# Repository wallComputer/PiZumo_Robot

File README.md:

# PiZumo_Robot

Git Folder to share hardware and software files for PiZumo Robot.

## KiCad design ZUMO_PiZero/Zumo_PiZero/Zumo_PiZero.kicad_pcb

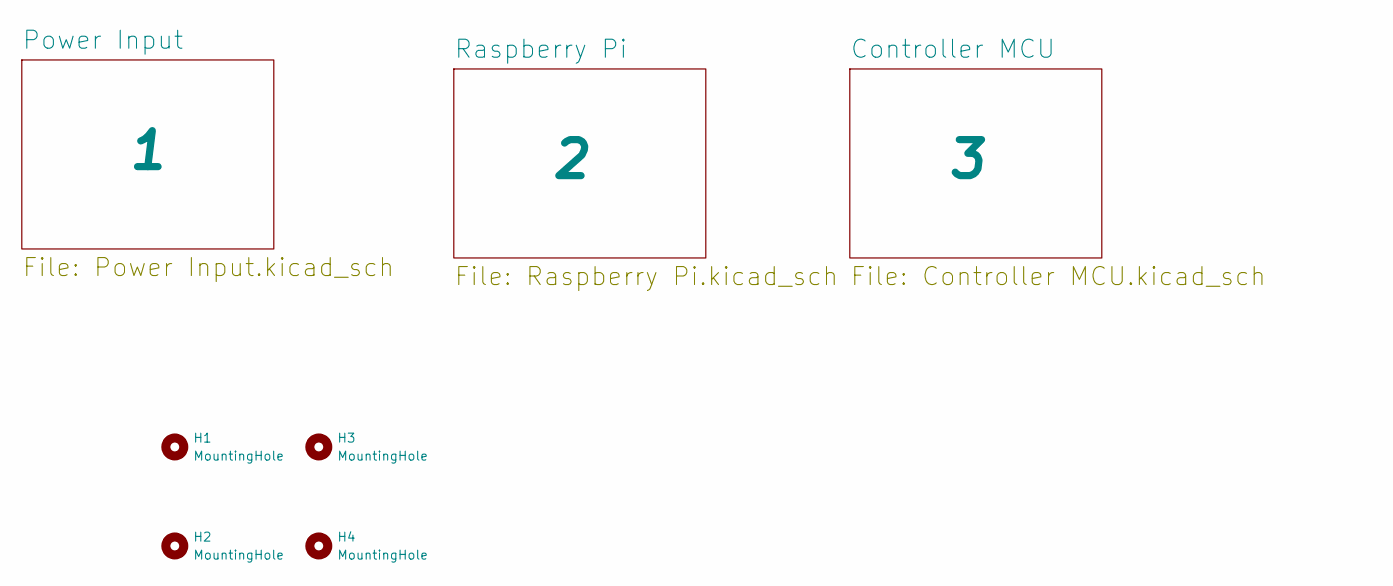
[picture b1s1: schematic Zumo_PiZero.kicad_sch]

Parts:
H1, H2, H3, H4: MountingHole; Zumo_Padded_Holes

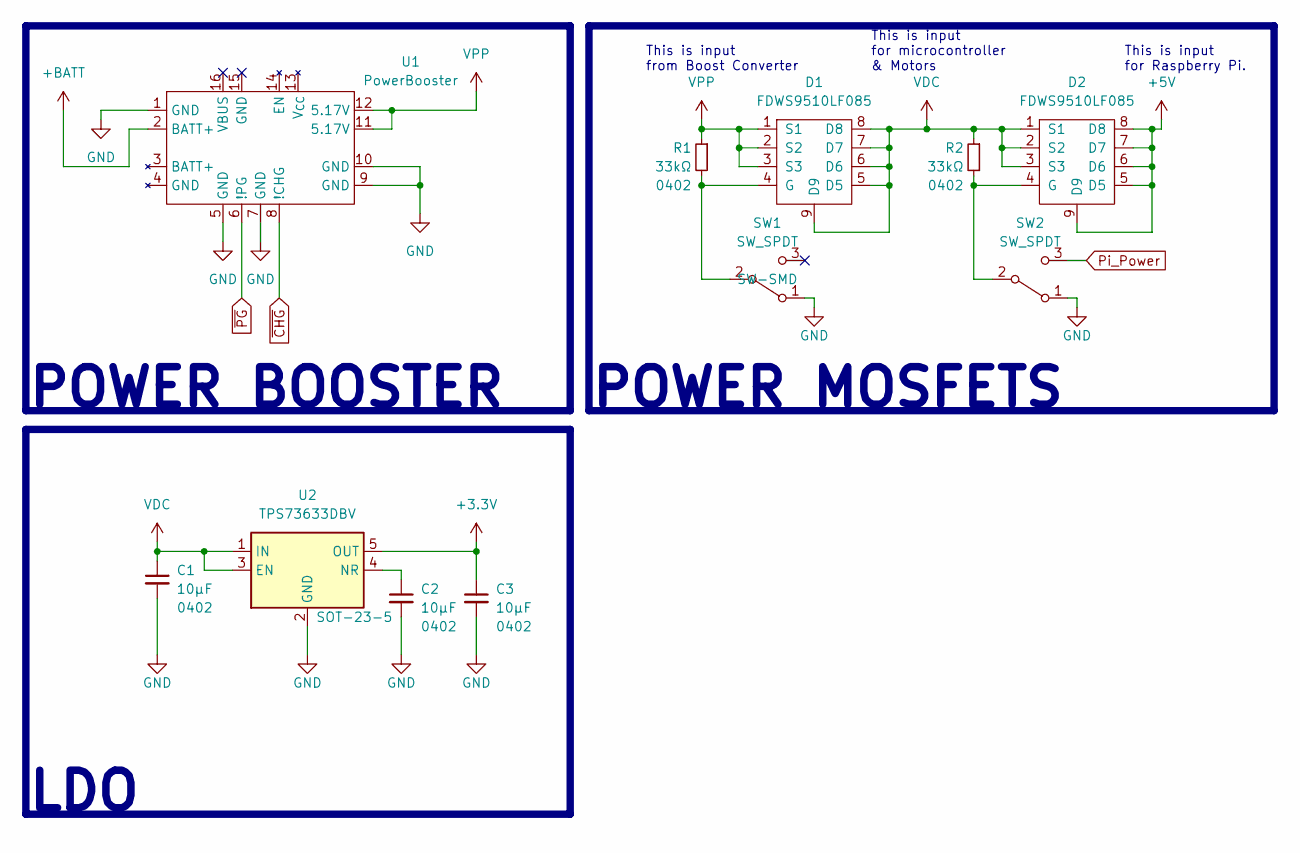
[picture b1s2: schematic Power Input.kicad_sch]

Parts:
C1, C2, C3: 10µF; C_0402_1005Metric; JLC 0402
D1, D2: FDWS9510LF085
R1, R2: 33kΩ; R_0402_1005Metric; JLC 0402
SW1, SW2: SW_SPDT; SW_SPDT_PCM12; JLC SW-SMD
U1: PowerBooster
U2: TPS73633DBV; SOT-23-5; JLC SOT-23-5

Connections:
+3V3: C3.1, U2.5 (OUT); also elsewhere on the board
+5V: D2.5 (D5), D2.6 (D6), D2.7 (D7), D2.8 (D8), D2.9 (D9); also elsewhere on the board
+BATT: U1.2 (BATT+); also elsewhere on the board
GND: C1.2, C2.2, C3.2, SW1.1 (A), SW2.1 (A), U1.1 (GND), U1.5 (GND), U1.7 (GND), U1.9 (GND), U1.10 (GND), U2.2 (GND); also elsewhere on the board
unnamed: C2.1, U2.4 (NR)
unnamed: D1.4 (G), R1.2, SW1.2 (B)
unnamed: D2.4 (G), R2.2, SW2.2 (B)
Pi_Power: SW2.3 (C); also elsewhere on the board
VDC: C1.1, D1.5 (D5), D1.6 (D6), D1.7 (D7), D1.8 (D8), D1.9 (D9), D2.1 (S1), D2.2 (S2), D2.3 (S3), R2.1, U2.1 (IN), U2.3 (EN); also elsewhere on the board
VPP: D1.1 (S1), D1.2 (S2), D1.3 (S3), R1.1, U1.11 (5.17V), U1.12 (5.17V)
~CHG: U1.8 (!CHG)
~PG: U1.6 (!PG)

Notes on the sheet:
This is input from Boost Converter
This is input for microcontroller & Motors
POWER MOSFETS
LDO
This is input for Raspberry Pi.
POWER BOOSTER

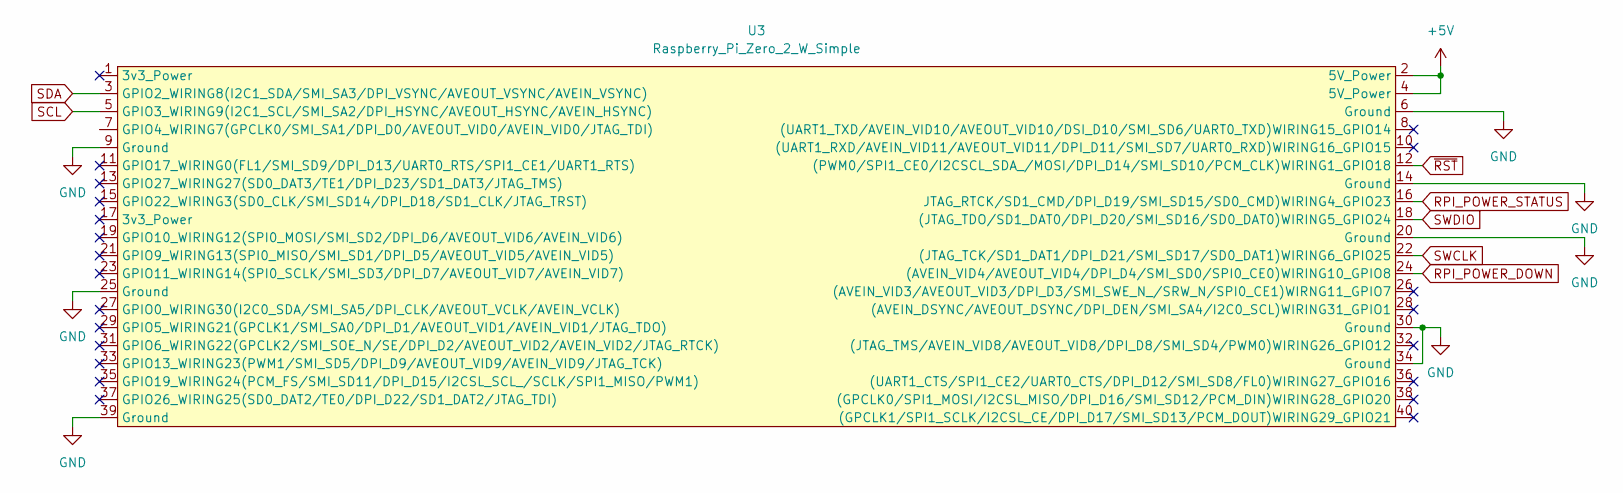
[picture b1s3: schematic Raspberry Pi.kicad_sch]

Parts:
U3: Raspberry_Pi_Zero_2_W_Simple; PinHeader_2x20_P2.54mm_Vertical

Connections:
+5V: U3.2 (5V_Power), U3.4 (5V_Power); also elsewhere on the board
GND: U3.6 (Ground), U3.9 (Ground), U3.14 (Ground), U3.20 (Ground), U3.25 (Ground), U3.30 (Ground), U3.34 (Ground), U3.39 (Ground); also elsewhere on the board
RPI_POWER_DOWN: U3.24 ((AVEIN_VID4/AVEOUT_VID4/DPI_D4/SMI_SD0/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); also elsewhere on the board
RPI_POWER_STATUS: U3.16 (JTAG_RTCK/SD1_CMD/DPI_D19/SMI_SD15/SD0_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); also elsewhere on the board
SCL: U3.5 (GPIO3_WIRING9(I2C1_SCL/SMI_SA2/DPI_HSYN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); also elsewhere on the board
SDA: U3.3 (GPIO2_WIRING8(I2C1_SDA/SMI_SA3/DPI_VSYN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); also elsewhere on the board
SWCLK: U3.22 ((JTAG_TCK/SD1_DAT1/DPI_D21/SMI_SD17/SD0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); also elsewhere on the board
SWDIO: U3.18 ((JTAG_TDO/SD1_DAT0/DPI_D20/SMI_SD16/SD0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); also elsewhere on the board
~RST: U3.12 ((PWM0/SPI1_CE0/I2CSCL_SDA_/MOSI/DPI_D14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); also elsewhere on the board

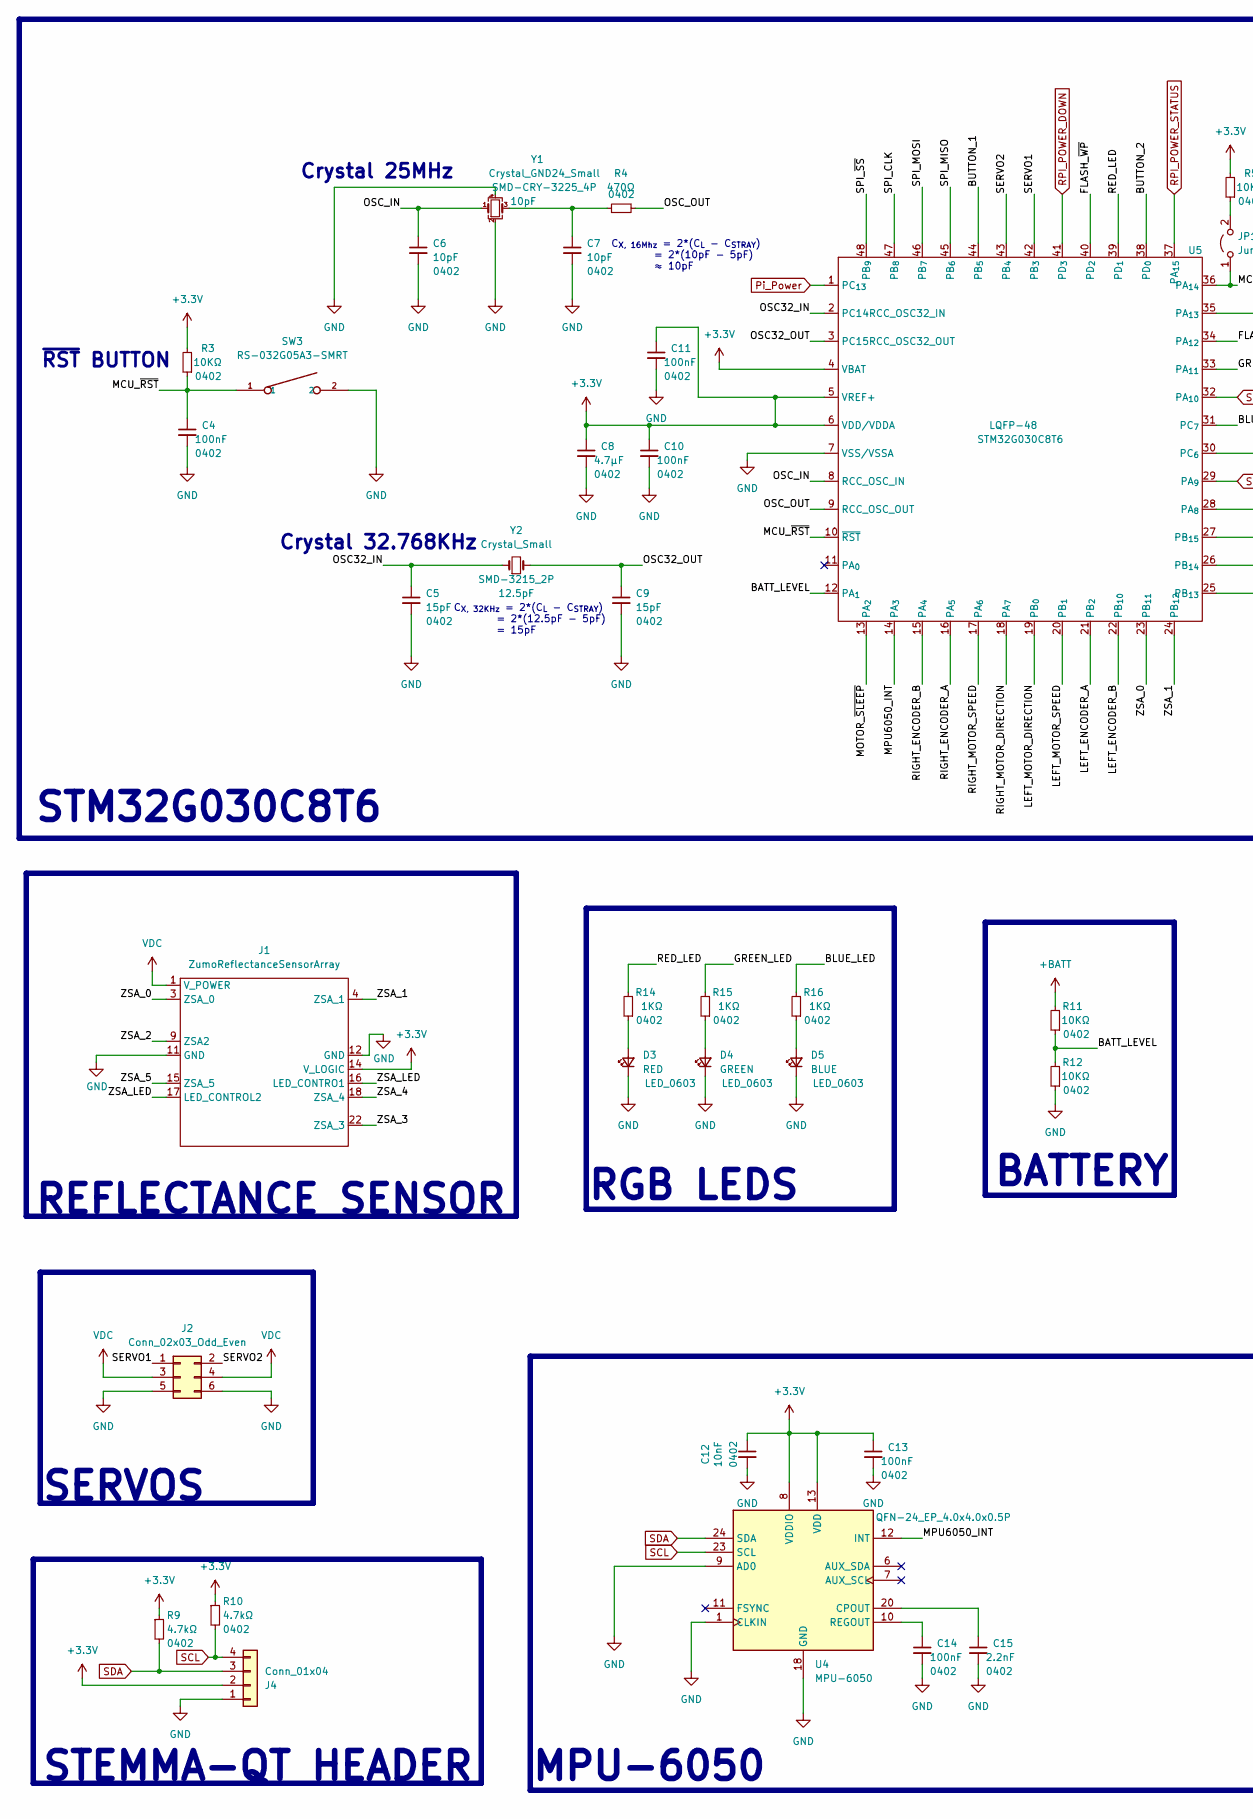
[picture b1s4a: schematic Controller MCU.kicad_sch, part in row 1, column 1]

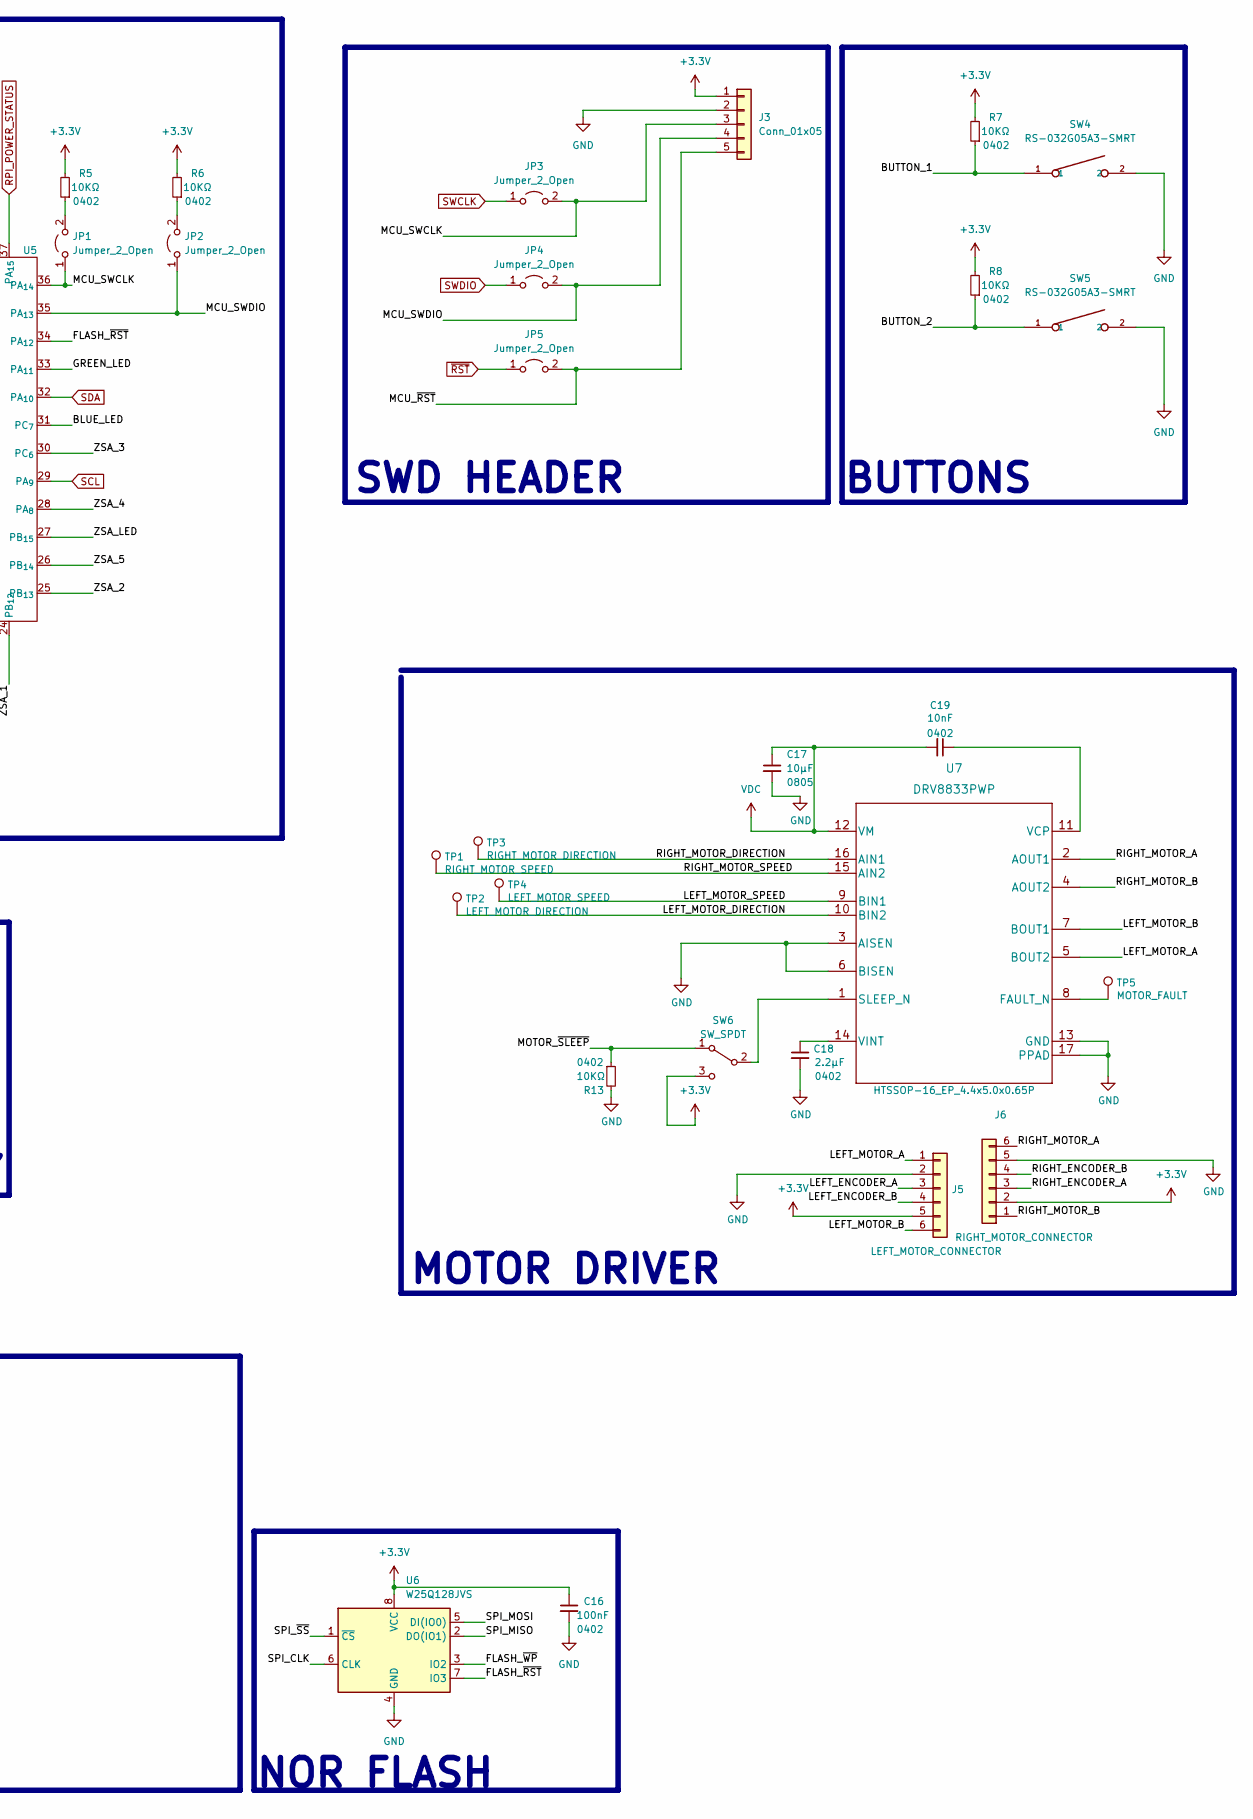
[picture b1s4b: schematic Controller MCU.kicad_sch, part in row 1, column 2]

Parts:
C4, C10, C11, C13, C14, C16: 100nF; C_0402_1005Metric; JLC 0402
C5, C9: 15pF; C_0402_1005Metric; JLC 0402
C6, C7: 10pF; C_0402_1005Metric; JLC 0402
C8: 4.7µF; C_0402_1005Metric; JLC 0402
C12, C19: 10nF; C_0402_1005Metric; JLC 0402
C15: 2.2nF; C_0402_1005Metric; JLC 0402
C17: 10µF; C_0805_2012Metric; JLC 0805
C18: 2.2µF; C_0402_1005Metric; JLC 0402
D3: RED; LED_0603_1608Metric; JLC LED_0603
D4: GREEN; LED_0603_1608Metric; JLC LED_0603
D5: BLUE; LED_0603_1608Metric; JLC LED_0603
J1: ZumoReflectanceSensorArray; PinSocket_2x12_P2.54mm_Vertical
J2: Conn_02x03_Odd_Even; PinHeader_2x03_P2.54mm_Vertical
J3: Conn_01x05; PinHeader_1x05_P2.54mm_Vertical
J4: Conn_01x04; JST-1x04_1mm; JLC SMD_P=1mm
J5: LEFT_MOTOR_CONNECTOR; PinHeader_1x06_P2.54mm_Vertical
J6: RIGHT_MOTOR_CONNECTOR; PinHeader_1x06_P2.54mm_Vertical
JP1, JP2, JP3, JP4, JP5: Jumper_2_Open; SolderJumper-2_P1.3mm_Open_Pad1.0x1.5mm
R3, R5, R6, R7, R8, R11, R12, R13: 10KΩ; R_0402_1005Metric; JLC 0402
R4: 470Ω; R_0402_1005Metric; JLC 0402
R9, R10: 4.7kΩ; R_0402_1005Metric; JLC 0402
R14, R15, R16: 1KΩ; R_0402_1005Metric; JLC 0402
SW3, SW4, SW5: RS-032G05A3-SMRT; SW_RS-032G05A3-SMRT
SW6: SW_SPDT; SW_SPDT_PCM12; JLC SW-SMD
TP1: RIGHT_MOTOR_SPEED; TestPoint_Pad_1.0x1.0mm
TP2: LEFT_MOTOR_DIRECTION; TestPoint_Pad_1.0x1.0mm
TP3: RIGHT_MOTOR_DIRECTION; TestPoint_Pad_1.0x1.0mm
TP4: LEFT_MOTOR_SPEED; TestPoint_Pad_1.0x1.0mm
TP5: MOTOR_FAULT; TestPoint_Pad_1.0x1.0mm
U4: MPU-6050; InvenSense_QFN-24_4x4mm_P0.5mm; JLC QFN-24_EP_4.0x4.0x0.5P
U5: STM32G030C8T6; LQFP-48_7x7mm_P0.5mm; JLC LQFP-48
U6: W25Q128JVS; SOIC-8_5.275x5.275mm_P1.27mm; JLC SOIC-8_5.3x5.3x1.27P
U7: DRV8833PWP; JLC HTSSOP-16_EP_4.4x5.0x0.65P
Y1: Crystal_GND24_Small; Crystal_SMD_3225-4Pin_3.2x2.5mm; JLC SMD-CRY-3225_4P
Y2: Crystal_Small; Crystal_SMD_3215-2Pin_3.2x1.5mm; JLC SMD-3215_2P

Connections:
+3V3: C8.1, C10.1, C11.1, C12.1, C13.1, C16.1, J1.14 (V_LOGIC), J3.1, J4.2, J5.5, J6.2, R3.2, R5.2, R6.2, R7.2, R8.2, R9.1, R10.1, SW6.3 (C), U4.8 (VDDIO), U4.13 (VDD), U5.4 (VBAT), U5.5 (VREF+), U5.6 (VDD/VDDA), U6.8 (VCC); also elsewhere on the board
+BATT: R11.2; also elsewhere on the board
/Controller MCU/BATT_LEVEL: R11.1, R12.2, U5.12 (PA_{1})
/Controller MCU/BLUE_LED: R16.2, U5.31 (PC_{7})
/Controller MCU/BUTTON_1: R7.1, SW4.1, U5.44 (PB_{5})
/Controller MCU/BUTTON_2: R8.1, SW5.1, U5.38 (PD_{0})
/Controller MCU/FLASH_~RST: U5.34 (PA_{12}), U6.7 (IO3)
/Controller MCU/FLASH_~WP: U5.40 (PD_{2}), U6.3 (IO2)
/Controller MCU/GREEN_LED: R15.2, U5.33 (PA_{11})
/Controller MCU/LEFT_ENCODER_A: J5.3, U5.21 (PB_{2})
/Controller MCU/LEFT_ENCODER_B: J5.4, U5.22 (PB_{10})
/Controller MCU/LEFT_MOTOR_A: J5.1, U7.5 (BOUT2)
/Controller MCU/LEFT_MOTOR_B: J5.6, U7.7 (BOUT1)
/Controller MCU/LEFT_MOTOR_DIRECTION: TP2.1, U5.19 (PB_{0}), U7.10 (BIN2)
/Controller MCU/LEFT_MOTOR_SPEED: TP4.1, U5.20 (PB_{1}), U7.9 (BIN1)
/Controller MCU/MCU_SWCLK: J3.3, JP1.1 (A), JP3.2 (B), U5.36 (PA_{14})
/Controller MCU/MCU_SWDIO: J3.4, JP2.1 (A), JP4.2 (B), U5.35 (PA_{13})
/Controller MCU/MCU_~RST: C4.1, J3.5, JP5.2 (B), R3.1, SW3.1, U5.10 (~RST)
/Controller MCU/MOTOR_~SLEEP: R13.1, SW6.1 (A), U5.13 (PA_{2})
/Controller MCU/MPU6050_INT: U4.12 (INT), U5.14 (PA_{3})
/Controller MCU/OSC32_IN: C5.1, U5.2 (PC14RCC_OSC32_IN), Y2.1
/Controller MCU/OSC32_OUT: C9.1, U5.3 (PC15RCC_OSC32_OUT), Y2.2
/Controller MCU/OSC_IN: C6.1, U5.8 (RCC_OSC_IN), Y1.1
/Controller MCU/OSC_OUT: R4.2, U5.9 (RCC_OSC_OUT)
/Controller MCU/RED_LED: R14.2, U5.39 (PD_{1})
/Controller MCU/RIGHT_ENCODER_A: J6.3, U5.16 (PA_{5})
/Controller MCU/RIGHT_ENCODER_B: J6.4, U5.15 (PA_{4})
/Controller MCU/RIGHT_MOTOR_A: J6.6, U7.2 (AOUT1)
/Controller MCU/RIGHT_MOTOR_B: J6.1, U7.4 (AOUT2)
/Controller MCU/RIGHT_MOTOR_DIRECTION: TP3.1, U5.18 (PA_{7}), U7.16 (AIN1)
/Controller MCU/RIGHT_MOTOR_SPEED: TP1.1, U5.17 (PA_{6}), U7.15 (AIN2)
/Controller MCU/SERVO1: J2.1, U5.42 (PB_{3})
/Controller MCU/SERVO2: J2.2, U5.43 (PB_{4})
/Controller MCU/SPI_CLK: U5.47 (PB_{8}), U6.6 (CLK)
/Controller MCU/SPI_MISO: U5.45 (PB_{6}), U6.2 (DO(IO1))
/Controller MCU/SPI_MOSI: U5.46 (PB_{7}), U6.5 (DI(IO0))
/Controller MCU/SPI_~SS: U5.48 (PB_{9}), U6.1 (~CS)
/Controller MCU/ZSA_0: J1.3 (ZSA_0), U5.23 (PB_{11})
/Controller MCU/ZSA_1: J1.4 (ZSA_1), U5.24 (PB_{12})
/Controller MCU/ZSA_2: J1.9 (ZSA2), U5.25 (PB_{13})
/Controller MCU/ZSA_3: J1.22 (ZSA_3), U5.30 (PC_{6})
/Controller MCU/ZSA_4: J1.18 (ZSA_4), U5.28 (PA_{8})
/Controller MCU/ZSA_5: J1.15 (ZSA_5), U5.26 (PB_{14})
/Controller MCU/ZSA_LED: J1.16 (LED_CONTRO1), J1.17 (LED_CONTROL2), U5.27 (PB_{15})
GND: C4.2, C5.2, C6.2, C7.2, C8.2, C9.2, C10.2, C11.2, C12.2, C13.2, C14.2, C15.2, C16.2, C17.2, C18.2, D3.1 (K), D4.1 (K), D5.1 (K), J1.11 (GND), J1.12 (GND), J2.5, J2.6, J3.2, J4.1, J5.2, J6.5, R12.1, R13.2, SW3.2, SW4.2, SW5.2, U4.1 (CLKIN), U4.9 (AD0), U4.18 (GND), U5.7 (VSS/VSSA), U6.4 (GND), U7.3 (AISEN), U7.6 (BISEN), U7.13 (GND), U7.17 (PPAD), Y1.2, Y1.4; also elsewhere on the board
unnamed: C7.1, R4.1, Y1.3
unnamed: C14.1, U4.10 (REGOUT)
unnamed: C15.1, U4.20 (CPOUT)
unnamed: C18.1, U7.14 (VINT)
unnamed: C19.1, U7.11 (VCP)
unnamed: D3.2 (A), R14.1
unnamed: D4.2 (A), R15.1
unnamed: D5.2 (A), R16.1
unnamed: JP1.2 (B), R5.1
unnamed: JP2.2 (B), R6.1
unnamed: SW6.2 (B), U7.1 (SLEEP_N)
unnamed: TP5.1, U7.8 (FAULT_N)
Pi_Power: U5.1 (PC_{13}); also elsewhere on the board
RPI_POWER_DOWN: U5.41 (PD_{3}); also elsewhere on the board
RPI_POWER_STATUS: U5.37 (PA_{15}); also elsewhere on the board
SCL: J4.4, R10.2, U4.23 (SCL), U5.29 (PA_{9}); also elsewhere on the board
SDA: J4.3, R9.2, U4.24 (SDA), U5.32 (PA_{10}); also elsewhere on the board
SWCLK: JP3.1 (A); also elsewhere on the board
SWDIO: JP4.1 (A); also elsewhere on the board
VDC: C17.1, C19.2, J1.1 (V_POWER), J2.3, J2.4, U7.12 (VM); also elsewhere on the board
~RST: JP5.1 (A); also elsewhere on the board

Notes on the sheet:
Crystal 32.768KHz
C_{X, 16Mhz} = 2*(C_{L} - C_{STRAY}) = 2*(10pF - 5pF) ≈ 10pF
NOR FLASH
C_{X, 32KHz} = 2*(C_{L} - C_{STRAY}) = 2*(12.5pF - 5pF) = 15pF
SWD HEADER
REFLECTANCE SENSOR
MOTOR DRIVER
SERVOS
STM32G030C8T6
RGB LEDS
STEMMA-QT HEADER
~{RST} BUTTON
MPU-6050
BATTERY
BUTTONS
Crystal 25MHz

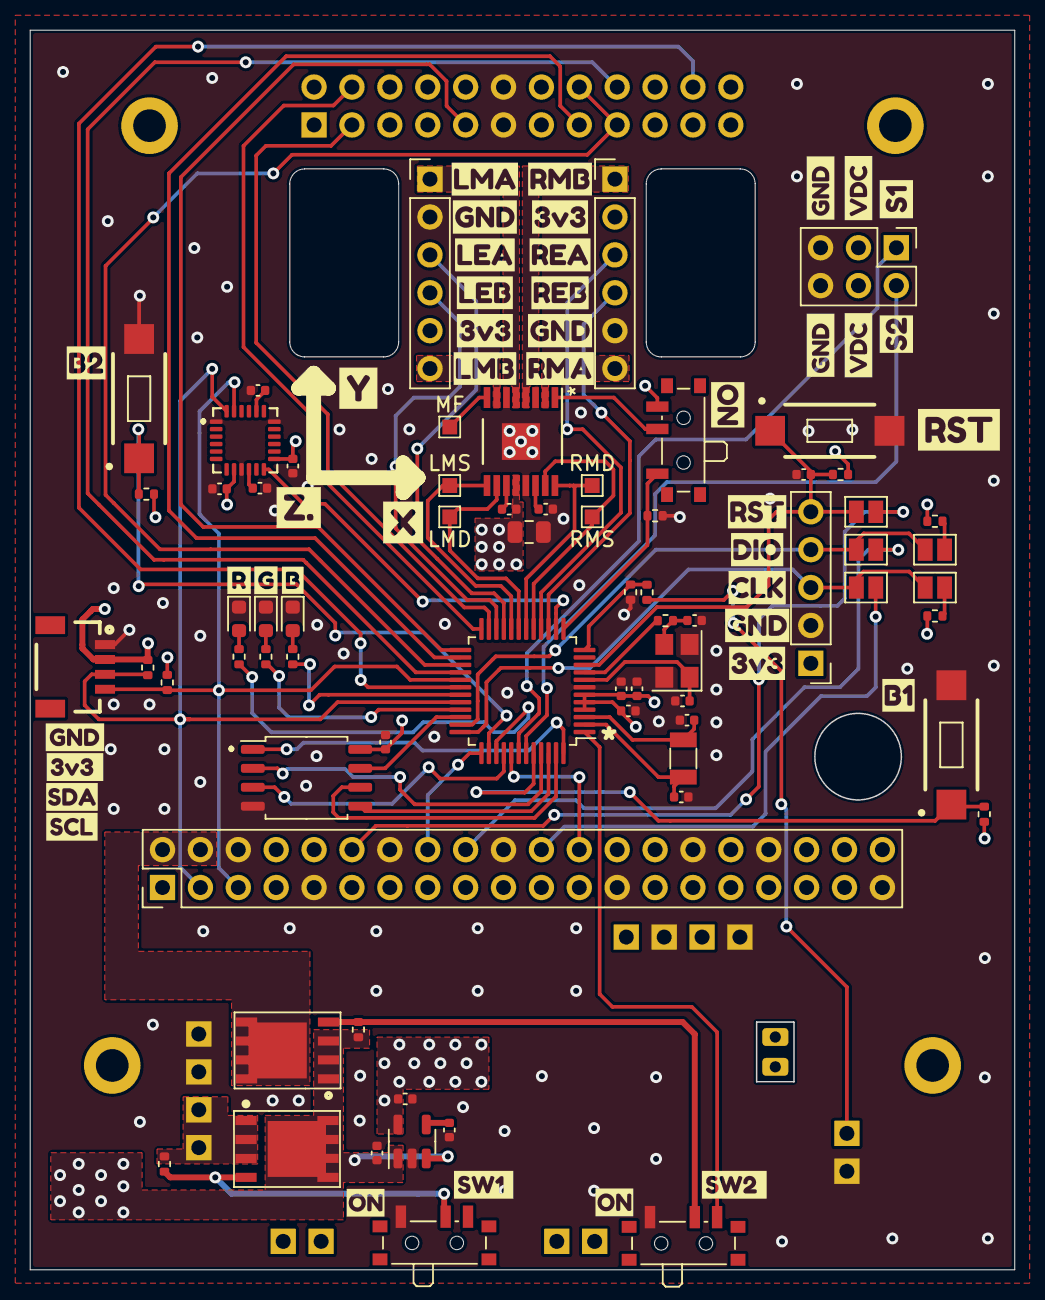
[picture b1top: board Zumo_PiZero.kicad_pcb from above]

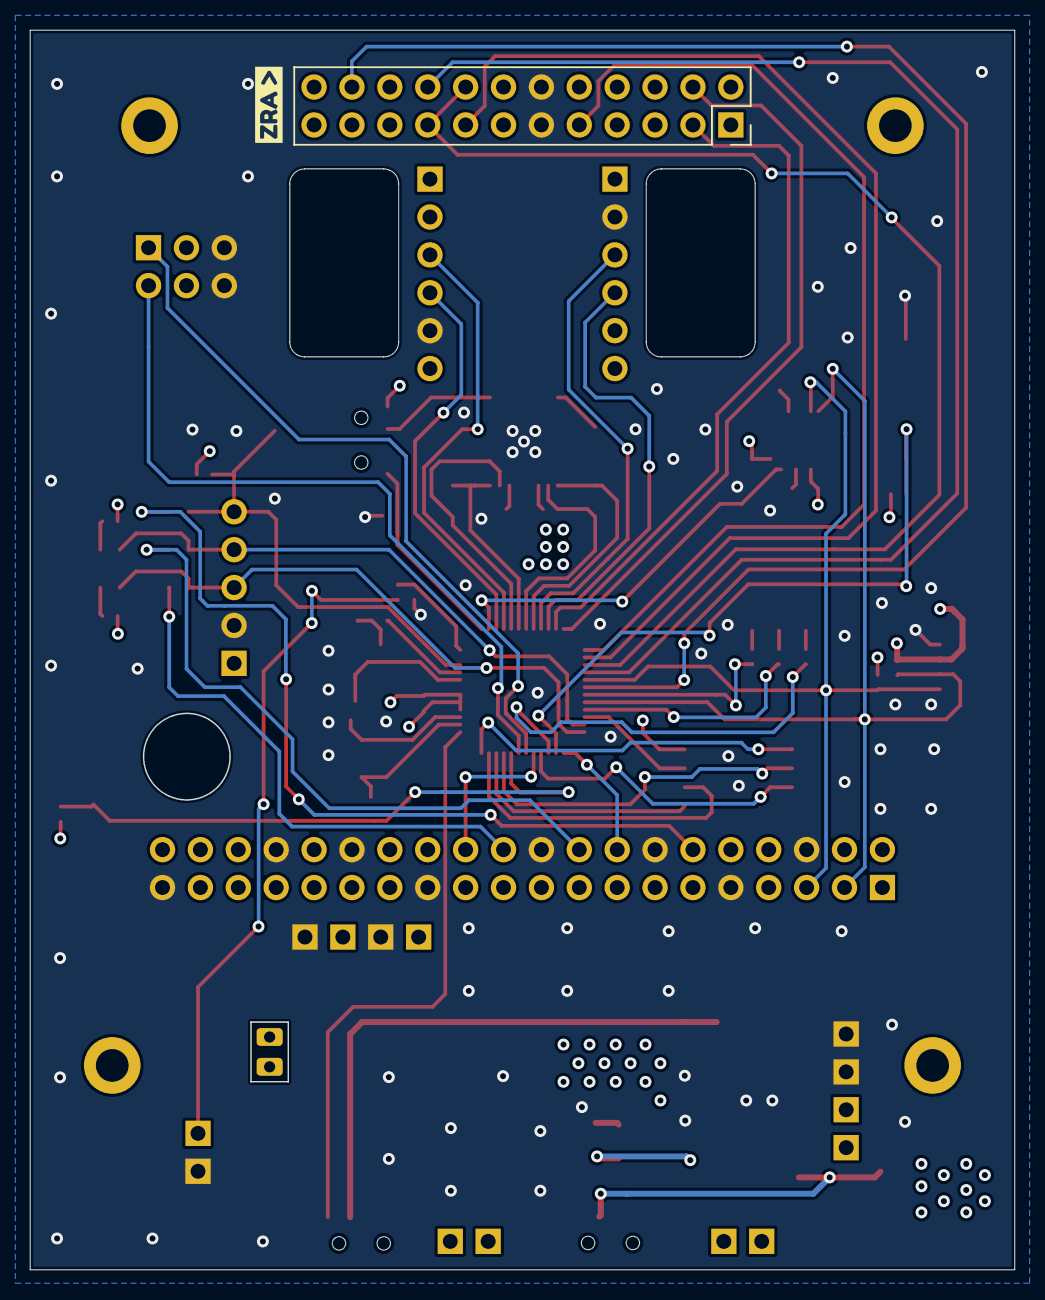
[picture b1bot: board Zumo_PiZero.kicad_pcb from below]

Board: 4 copper layers, 66.0 x 83.1 mm, 117 parts (2 on the bottom side), 71 nets.

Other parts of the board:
kibuzzard-6296F2B1: G***; kibuzzard-6296F2B1
kibuzzard-6296F4D2: G***; kibuzzard-6296F4D2
kibuzzard-6296F5A0: G***; kibuzzard-6296F5A0
kibuzzard-6296F5AA: G***; kibuzzard-6296F5AA
kibuzzard-6296F5B2: G***; kibuzzard-6296F5B2
kibuzzard-6296F5BA: G***; kibuzzard-6296F5BA
kibuzzard-6296F9F2: G***; kibuzzard-6296F9F2
kibuzzard-6296F43B: G***; kibuzzard-6296F43B
kibuzzard-6296F44E: G***; kibuzzard-6296F44E
kibuzzard-6296F46A: G***; kibuzzard-6296F46A
kibuzzard-6296F48A: G***; kibuzzard-6296F48A
kibuzzard-6296F50A: G***; kibuzzard-6296F50A
kibuzzard-6296F61E: G***; kibuzzard-6296F61E
kibuzzard-6296F73C: G***; kibuzzard-6296F73C
kibuzzard-6296F75E: G***; kibuzzard-6296F75E
kibuzzard-6296F296: G***; kibuzzard-6296F296
kibuzzard-6296F425: G***; kibuzzard-6296F425
kibuzzard-6296F446: G***; kibuzzard-6296F446
kibuzzard-6296F456: G***; kibuzzard-6296F456
kibuzzard-6296F463: G***; kibuzzard-6296F463
kibuzzard-6296F475: G***; kibuzzard-6296F475
kibuzzard-6296F481: G***; kibuzzard-6296F481
kibuzzard-6296F631: G***; kibuzzard-6296F631
kibuzzard-6296F701: G***; kibuzzard-6296F701
kibuzzard-6296FB5C: G***; kibuzzard-6296FB5C
kibuzzard-6296FB81: G***; kibuzzard-6296FB81
kibuzzard-6296FB94: G***; kibuzzard-6296FB94
kibuzzard-6296FCA0: G***; kibuzzard-6296FCA0
kibuzzard-6296FCE8: G***; kibuzzard-6296FCE8
kibuzzard-6296FD01: G***; kibuzzard-6296FD01
kibuzzard-6296FD9C: G***; kibuzzard-6296FD9C
kibuzzard-6296FD26, kibuzzard-6296FD26#2: G***; kibuzzard-6296FD26
kibuzzard-6296FD33, kibuzzard-6296FD33#2: G***; kibuzzard-6296FD33
kibuzzard-62975A1B: G***; kibuzzard-62975A1B
kibuzzard-62975D6B: G***; kibuzzard-62975D6B
kibuzzard-629759BC: G***; kibuzzard-629759BC
kibuzzard-629759C6: G***; kibuzzard-629759C6
kibuzzard-629805D4: G***; kibuzzard-629805D4
kibuzzard-629805DB: G***; kibuzzard-629805DB
kibuzzard-629810EF: G***; kibuzzard-629810EF

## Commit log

2022-06-19 First README.md
2022-06-19 Added Hardware Files
2022-06-19 Removed
2022-06-19 Removed Gerber
2022-06-19 Removed Assembly
